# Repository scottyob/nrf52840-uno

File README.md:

# nrf52840-uno
A development board for the nRF52840 in a Uno form factor.  Idea is to test nRF52 components before using on larger projects.  Has USB-C support
and a LiPo charge controller.

Using the Holyiot 18010 module due to not wanting to have the know-how of antenna design just yet!

## Battery

Please ensure that a 1S LiPo battery is used with at least a capacity of 450mA (or ability to charge at a rate of 450mA)

## Flashing

Something like the Adafruit Pogo probe (4 pin version), can be used to flash this using SWD.  I used a rPi Pico and [DebugProbe](https://github.com/raspberrypi/debugprobe)

**Quickstart:**
```
openocd -f interface/cmsis-dap.cfg -f target/nrf52.cfg -c "init"
[scott@sob-desktop Adafruit_Adalink]$ openocd -f interface/cmsis-dap.cfg -f target/nrf52.cfg -c "init"
Open On-Chip Debugger 0.12.0
Licensed under GNU GPL v2
For bug reports, read
	http://openocd.org/doc/doxygen/bugs.html
Info : auto-selecting first available session transport "swd". To override use 'transport select <transport>'.
Info : Using CMSIS-DAPv2 interface with VID:PID=0x2e8a:0x000c, serial=E66130100F7FA32B
Info : CMSIS-DAP: SWD supported
Info : CMSIS-DAP: Atomic commands supported
Info : CMSIS-DAP: Test domain timer supported
Info : CMSIS-DAP: FW Version = 2.0.0
Info : CMSIS-DAP: Interface Initialised (SWD)
Info : SWCLK/TCK = 0 SWDIO/TMS = 0 TDI = 0 TDO = 0 nTRST = 0 nRESET = 0
Info : CMSIS-DAP: Interface ready
Info : clock speed 1000 kHz
Info : SWD DPIDR 0x2ba01477
Info : [nrf52.cpu] Cortex-M4 r0p1 processor detected
Info : [nrf52.cpu] target has 6 breakpoints, 4 watchpoints
Info : starting gdb server for nrf52.cpu on 3333
Info : Listening on port 3333 for gdb connections
Info : Listening on port 6666 for tcl connections
Info : Listening on port 4444 for telnet connections

(seperate terminal)
(env) [scott@sob-desktop local-scott]$ telnet localhost 4444
Trying ::1...
telnet: connect to address ::1: Connection refused
Trying 127.0.0.1...
Connected to localhost.
Escape character is '^]'.
Open On-Chip Debugger
> nrf5 info
nRF52840-xxAA(build code: D0) 1024kB Flash, 256kB RAM

halt
nrf5 mass_erase
flash write_image pca10056_bootloader-0.2.11_s140_6.1.1.hex
flash verify_image pca10056_bootloader-0.2.11_s140_6.1.1.hex
reset run

```

Programming with Arduino:
```
Adafruit mRF52 -> Nordic nRF52840 DK (ours is similar to this)
Tools -> Programmer -> Bootloader DFU
Burn Bootloader
```

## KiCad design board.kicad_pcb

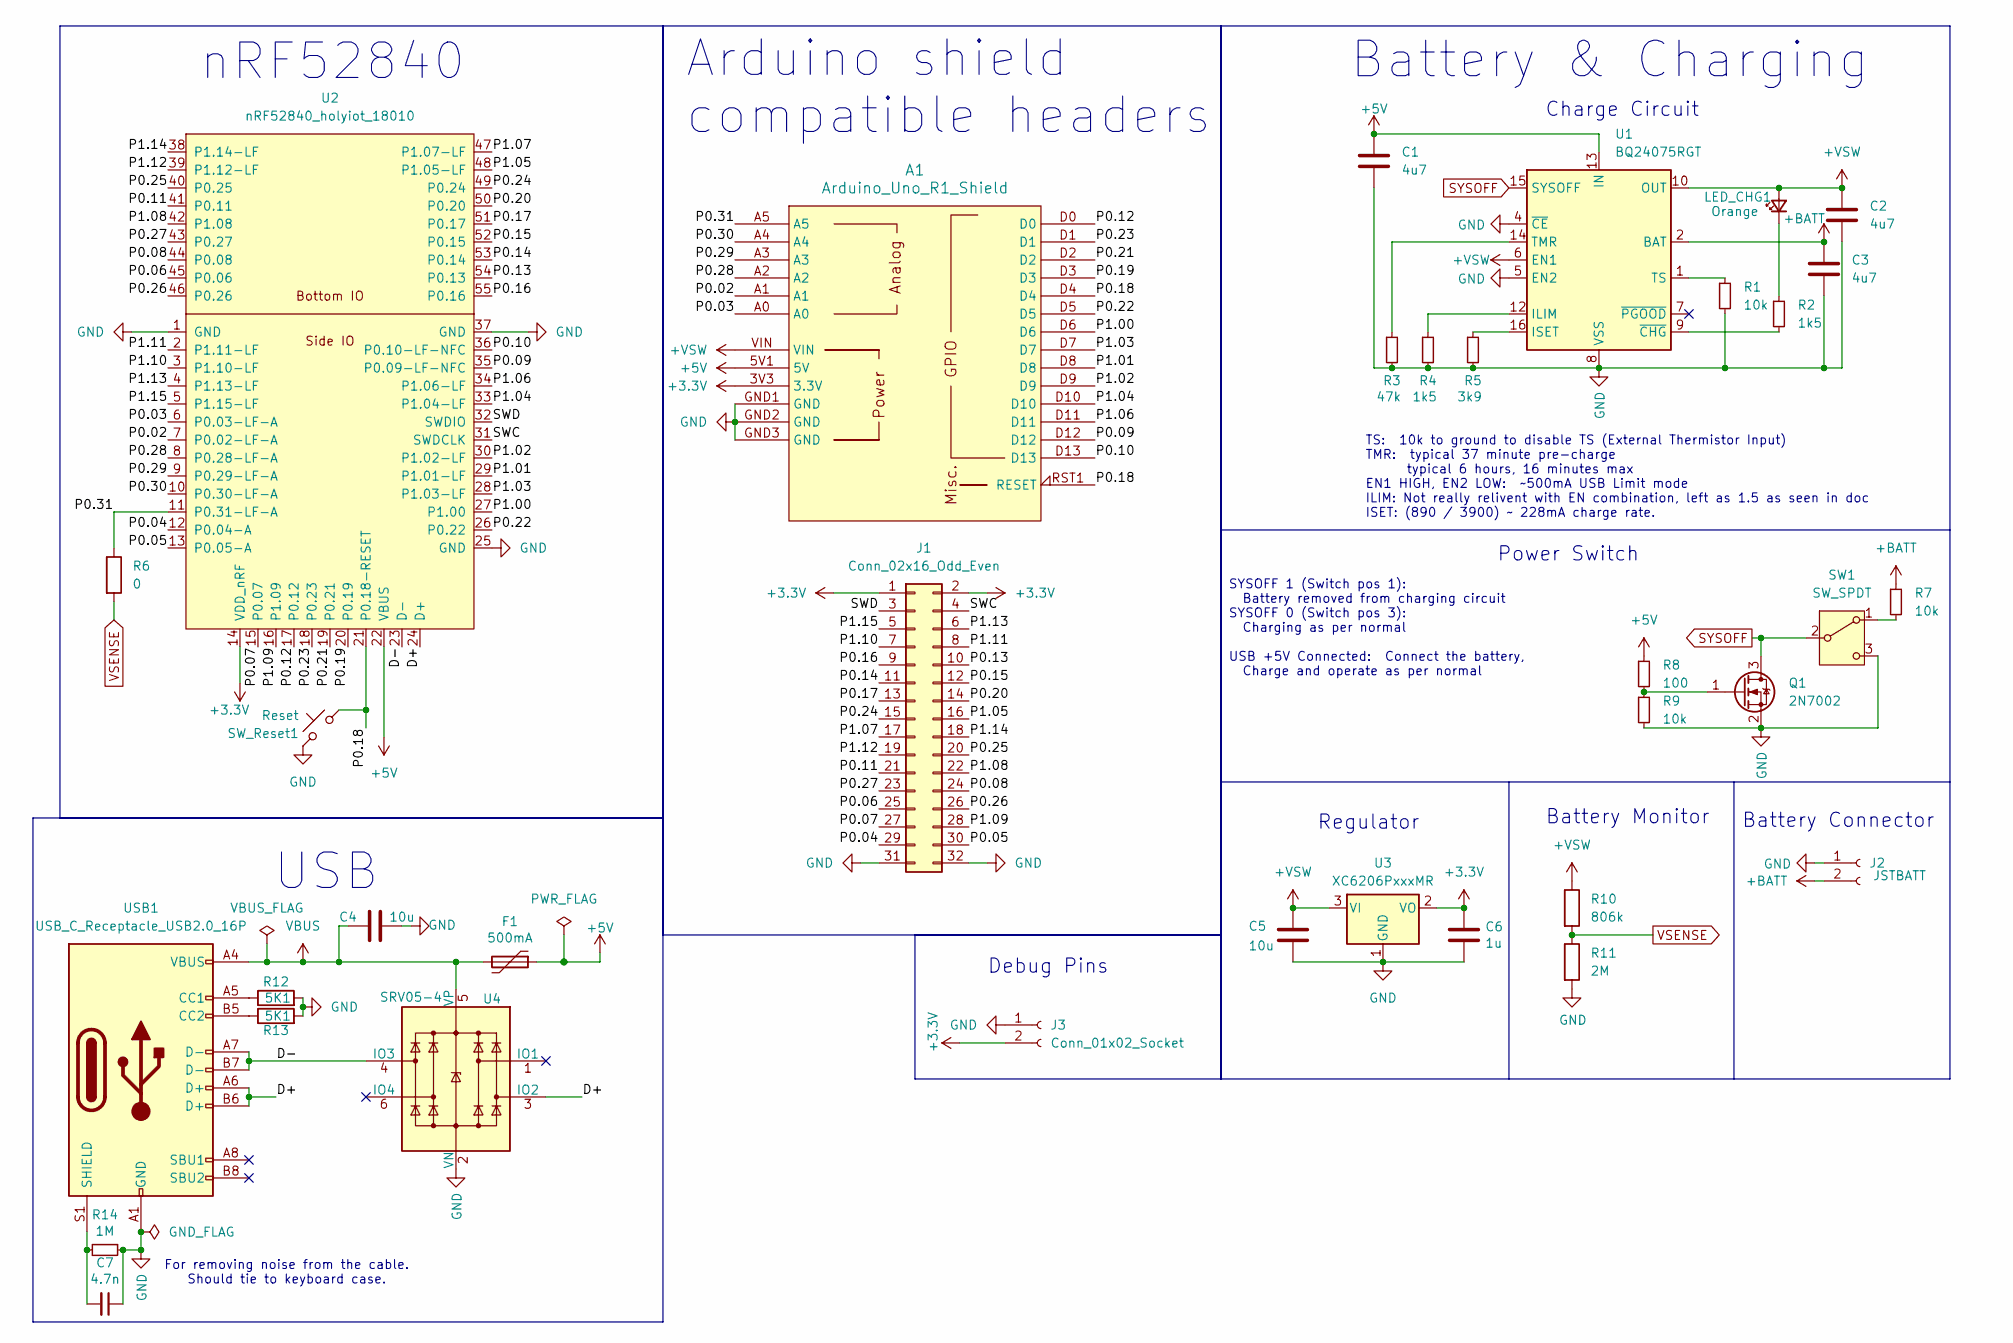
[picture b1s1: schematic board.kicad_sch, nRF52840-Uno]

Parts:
A1: Arduino_Uno_R1_Shield; Arduino_Uno_R2_Shield
C1, C2, C3: 4u7; C_0603_1608Metric
C4, C5: 10u; C_0603_1608Metric; MPN CL10A106KP8NNNC; JLCSMT C19702
C6: 1u; C_0603_1608Metric; MPN CL10A105KB8NNNC; LCSC C15849
C7: 4.7n; C_0805_2012Metric
F1: 500mA; Fuse_0805_2012Metric; MPN SMD0805-050; JLCSMT C66452
J1: Conn_02x16_Odd_Even; PinHeader_2x16_P2.54mm_Vertical
J2: JSTBATT; JST_PH_S2B-PH-K_1x02_P2.00mm_Horizontal
J3: Conn_01x02_Socket; PinHeader_1x02_P2.54mm_Vertical
LED_CHG1: Orange; LED_0603_1608Metric_Pad1.05x0.95mm_HandSolder
Q1: 2N7002; SOT-23
R1, R7, R9: 10k; R_0603_1608Metric_Pad0.98x0.95mm_HandSolder
R2, R4: 1k5; R_0603_1608Metric_Pad0.98x0.95mm_HandSolder
R3: 47k; R_0603_1608Metric_Pad0.98x0.95mm_HandSolder
R5: 3k9; R_0603_1608Metric_Pad0.98x0.95mm_HandSolder
R6: 0; R_0603_1608Metric_Pad0.98x0.95mm_HandSolder
R8: 100; R_0603_1608Metric_Pad0.98x0.95mm_HandSolder
R10: 806k; R_0603_1608Metric_Pad0.98x0.95mm_HandSolder
R11: 2M; R_0603_1608Metric_Pad0.98x0.95mm_HandSolder
R12, R13: 5K1; R_0603_1608Metric_Pad0.98x0.95mm_HandSolder
R14: 1M; R_0603_1608Metric_Pad0.98x0.95mm_HandSolder
SW1: SW_SPDT; SW_MSK12C02-HB
SW_Reset1: Reset; SW_Push_1P1T_NO_6x6mm_H9.5mm
U1: BQ24075RGT; VQFN-16-1EP_3x3mm_P0.5mm_EP1.6x1.6mm
U2: nRF52840_holyiot_18010
U3: XC6206PxxxMR; SOT-23-3
U4: SRV05-4; SOT-23-6; MPN SRV05-4-P-T7; JLCSMT C85364
USB1: USB_C_Receptacle_USB2.0_16P; USB_C_Receptacle_HRO_TYPE-C-31-M-12

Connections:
+3.3V: A1.3V3 (3.3V), C6.2, J1.1, J1.2, J3.2, U2.14 (VDD_nRF), U3.2 (VO)
+5V: A1.5V1 (5V), C1.1, F1.1, R8.1, U1.13 (IN), U2.22 (VBUS)
+BATT: C3.1, J2.2, R7.1, U1.2 (BAT), U1.3 (BAT)
+VSW: A1.VIN, C2.1, C5.1, LED_CHG1.2 (A), R10.1, U1.6 (EN1), U1.10 (OUT), U1.11 (OUT), U3.3 (VI)
/D+: U2.24 (D+), U4.3 (IO2), USB1.A6 (D+), USB1.B6 (D+)
/D-: U2.23 (D-), U4.4 (IO3), USB1.A7 (D-), USB1.B7 (D-)
/P0.02: A1.A1, U2.7 (P0.02-LF-A)
/P0.03: A1.A0, U2.6 (P0.03-LF-A)
/P0.04: J1.29, U2.12 (P0.04-A)
/P0.05: J1.30, U2.13 (P0.05-A)
/P0.06: J1.25, U2.45 (P0.06)
/P0.07: J1.27, U2.15 (P0.07)
/P0.08: J1.24, U2.44 (P0.08)
/P0.09: A1.D12, U2.35 (P0.09-LF-NFC)
/P0.10: A1.D13, U2.36 (P0.10-LF-NFC)
/P0.11: J1.21, U2.41 (P0.11)
/P0.12: A1.D0, U2.17 (P0.12)
/P0.13: J1.10, U2.54 (P0.13)
/P0.14: J1.11, U2.53 (P0.14)
/P0.15: J1.12, U2.52 (P0.15)
/P0.16: J1.9, U2.55 (P0.16)
/P0.17: J1.13, U2.51 (P0.17)
/P0.18: A1.D4, A1.RST1 (RESET), SW_Reset1.2, U2.21 (P0.18-RESET)
/P0.19: A1.D3, U2.20 (P0.19)
/P0.20: J1.14, U2.50 (P0.20)
/P0.21: A1.D2, U2.19 (P0.21)
/P0.22: A1.D5, U2.26 (P0.22)
/P0.23: A1.D1, U2.18 (P0.23)
/P0.24: J1.15, U2.49 (P0.24)
/P0.25: J1.20, U2.40 (P0.25)
/P0.26: J1.26, U2.46 (P0.26)
/P0.27: J1.23, U2.43 (P0.27)
/P0.28: A1.A2, U2.8 (P0.28-LF-A)
/P0.29: A1.A3, U2.9 (P0.29-LF-A)
/P0.30: A1.A4, U2.10 (P0.30-LF-A)
/P0.31: A1.A5, R6.1, U2.11 (P0.31-LF-A)
/P1.00: A1.D6, U2.27 (P1.00)
/P1.01: A1.D8, U2.29 (P1.01-LF)
/P1.02: A1.D9, U2.30 (P1.02-LF)
/P1.03: A1.D7, U2.28 (P1.03-LF)
/P1.04: A1.D10, U2.33 (P1.04-LF)
/P1.05: J1.16, U2.48 (P1.05-LF)
/P1.06: A1.D11, U2.34 (P1.06-LF)
/P1.07: J1.17, U2.47 (P1.07-LF)
/P1.08: J1.22, U2.42 (P1.08)
/P1.09: J1.28, U2.16 (P1.09)
/P1.10: J1.7, U2.3 (P1.10-LF)
/P1.11: J1.8, U2.2 (P1.11-LF)
/P1.12: J1.19, U2.39 (P1.12-LF)
/P1.13: J1.6, U2.4 (P1.13-LF)
/P1.14: J1.18, U2.38 (P1.14-LF)
/P1.15: J1.5, U2.5 (P1.15-LF)
/SWC: J1.4, U2.31 (SWDCLK)
/SWD: J1.3, U2.32 (SWDIO)
GND: A1.GND1 (GND), A1.GND2 (GND), A1.GND3 (GND), C1.2, C2.2, C3.2, C4.1, C5.2, C6.1, C7.1, J1.31, J1.32, J2.1, J3.1, Q1.2 (S), R1.2, R3.2, R4.2, R5.2, R9.2, R11.2, R12.2, R13.2, R14.1, SW1.3 (C), SW_Reset1.1, U1.4 (~CE), U1.5 (EN2), U1.8 (VSS), U1.17 (VSS), U2.1 (GND), U2.25 (GND), U2.37 (GND), U3.1 (GND), U4.2 (VN), USB1.A1 (GND), USB1.A12 (GND), USB1.B1 (GND), USB1.B12 (GND)
unnamed: LED_CHG1.1 (K), R2.1
unnamed: Q1.1 (G), R8.2, R9.1
unnamed: R7.2, SW1.1 (A)
unnamed: R4.1, U1.12 (ILIM)
unnamed: R5.1, U1.16 (ISET)
unnamed: R3.1, U1.14 (TMR)
unnamed: R1.1, U1.1 (TS)
unnamed: R2.2, U1.9 (~CHG)
unnamed: R12.1, USB1.A5 (CC1)
unnamed: R13.1, USB1.B5 (CC2)
unnamed: C7.2, R14.2, USB1.S1 (SHIELD)
SYSOFF: Q1.3 (D), SW1.2 (B), U1.15 (SYSOFF)
VBUS: C4.2, F1.2, U4.5 (VP), USB1.A4 (VBUS), USB1.A9 (VBUS), USB1.B4 (VBUS), USB1.B9 (VBUS)
VSENSE: R6.2, R10.2, R11.1

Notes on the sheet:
USB
Regulator
SYSOFF 1 (Switch pos 1): Battery removed from charging circuit SYSOFF 0 (Switch pos 3): Charging as per normal USB +5V Connected: Connect the battery, Charge and operate as per normal
TS: 10k to ground to disable TS (External Thermistor Input) TMR: typical 37 minute pre-charge typical 6 hours, 16 minutes max EN1 HIGH, EN2 LOW: ~500mA USB Limit mode ILIM: Not really relivent with EN combination, left as 1.5 as seen in doc ISET: (890 / 3900) ~ 228mA charge rate.
Battery & Charging
Battery Connector
Battery Monitor
Charge Circuit
For removing noise from the cable. Should tie to keyboard case.
Arduino shield compatible headers
Debug Pins
Power Switch
nRF52840

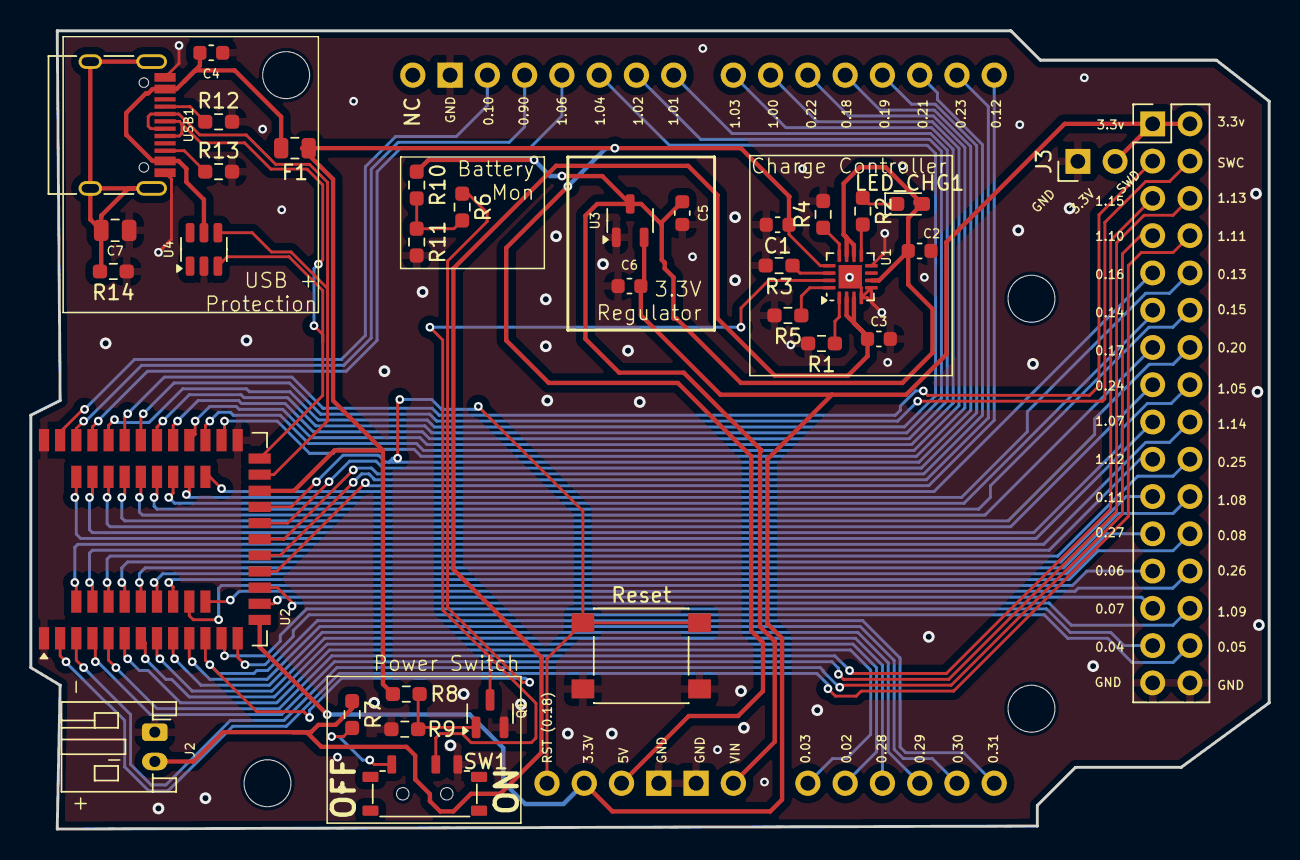
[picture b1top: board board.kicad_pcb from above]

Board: 2 copper layers, 84.4 x 54.4 mm, 35 parts (0 on the bottom side), 69 nets.

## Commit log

2024-08-13 Updated to revision 0.2, with Holyiot module on edge of board
2024-08-13 Updated silkscreen
2024-09-03 Added debug / programming pins
2025-04-02 Updated readme. Fixed silkscreen
2025-04-02 Fixed polarity of connector
